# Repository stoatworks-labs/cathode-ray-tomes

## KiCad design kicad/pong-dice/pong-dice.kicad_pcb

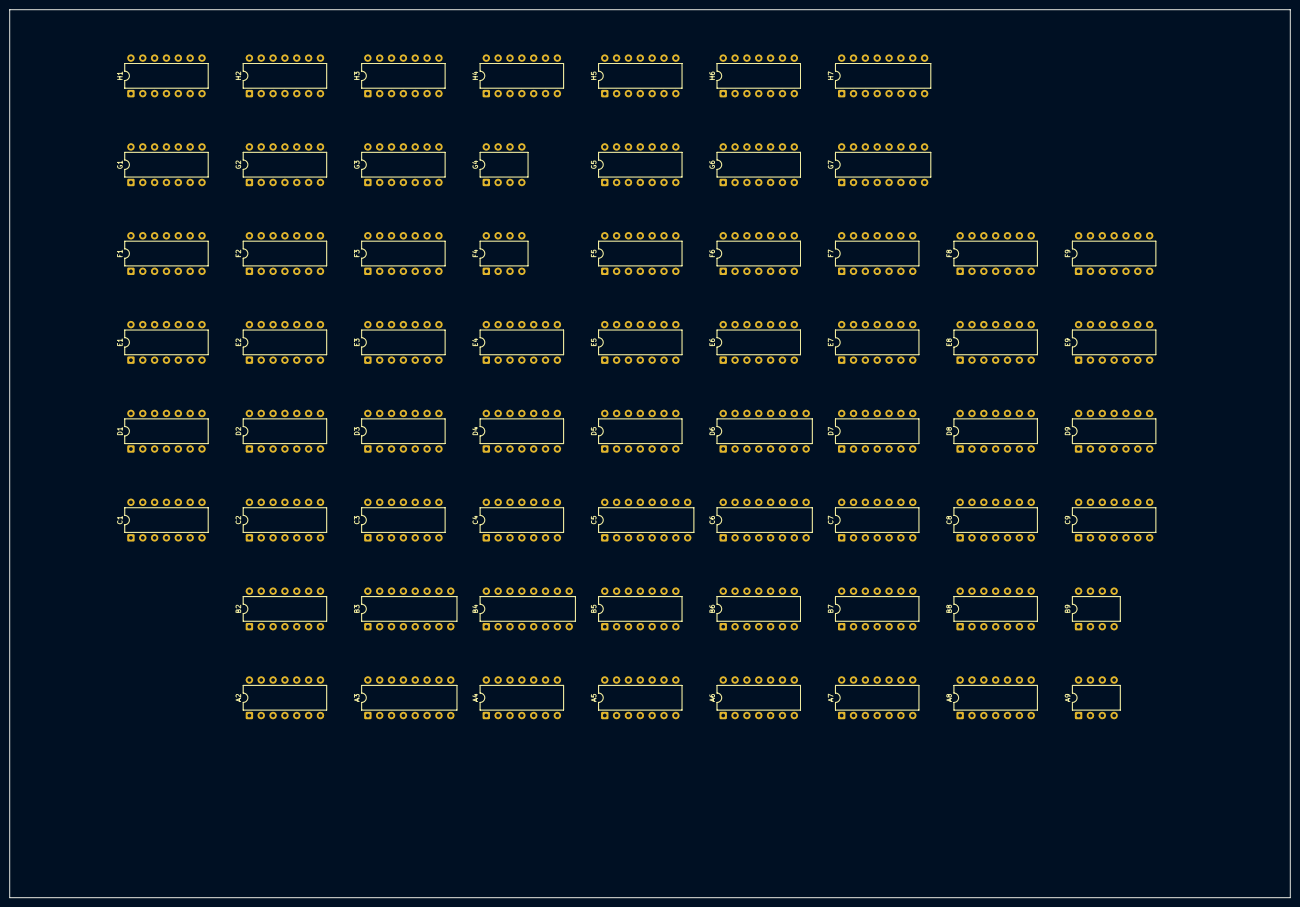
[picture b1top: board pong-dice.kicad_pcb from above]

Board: 2 copper layers, 274.6 x 190.4 mm, 66 parts (0 on the bottom side), 195 nets, no tracks yet.

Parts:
A2: 74107; DIP-14_W7.62mm
A3: 9316; DIP-16_W7.62mm
A4: 7486; DIP-14_W7.62mm
A5: 7474; DIP-14_W7.62mm
A6: 7450; DIP-14_W7.62mm
A7: 7420; DIP-14_W7.62mm
A8: 7493; DIP-14_W7.62mm
A9: 555; DIP-8_W7.62mm
B2, B7: 7400; DIP-14_W7.62mm
B3: 9316; DIP-16_W7.62mm
B4: 7483; DIP-16_W7.62mm
B5: 7474; DIP-14_W7.62mm
B6: 7450; DIP-14_W7.62mm
B8: 7493; DIP-14_W7.62mm
B9: 555; DIP-8_W7.62mm
C1, C3: 7400; DIP-14_W7.62mm
C2: 7474; DIP-14_W7.62mm
C4: 7410; DIP-14_W7.62mm
C5: 7448; DIP-16_W7.62mm
C6: 74153; DIP-16_W7.62mm
C7: 7490; DIP-14_W7.62mm
C8: 74107; DIP-14_W7.62mm
C9: 7404; DIP-14_W7.62mm
D1: 7404; DIP-14_W7.62mm
D2: 7402; DIP-14_W7.62mm
D3: 7430; DIP-14_W7.62mm
D4, D5, D8: 7410; DIP-14_W7.62mm
D6: 74153; DIP-16_W7.62mm
D7: 7490; DIP-14_W7.62mm
D9: 74107; DIP-14_W7.62mm
E1, E6: 7400; DIP-14_W7.62mm
E2: 7410; DIP-14_W7.62mm
E3, E5: 7427; DIP-14_W7.62mm
E4: 7404; DIP-14_W7.62mm
E7: 7474; DIP-14_W7.62mm
E8, E9: 7493; DIP-14_W7.62mm
F1, F8, F9: 7493; DIP-14_W7.62mm
F2: 7425; DIP-14_W7.62mm
F3, F6: 74107; DIP-14_W7.62mm
F4: 555; DIP-8_W7.62mm
F5: 7402; DIP-14_W7.62mm
F7: 7430; DIP-14_W7.62mm
G1: 7402; DIP-14_W7.62mm
G2: 7427; DIP-14_W7.62mm
G3: 7400; DIP-14_W7.62mm
G4: 555; DIP-8_W7.62mm
G5: 7410; DIP-14_W7.62mm
G6: 74107; DIP-14_W7.62mm
G7: 9316; DIP-16_W7.62mm
H1, H4, H5: 7400; DIP-14_W7.62mm
H2: 74107; DIP-14_W7.62mm
H3: 7474; DIP-14_W7.62mm
H6: 7420; DIP-14_W7.62mm
H7: 9316; DIP-16_W7.62mm

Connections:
+5V: A2.14, A3.16, A4.14, A5.14, A7.14, A8.5, A9.8, B2.14, B3.16, B4.5, B5.14, B7.14, B8.5, B9.8, C1.14, C2.14, C3.14, C4.14, C5.16, C6.16, C7.5, C8.14, C9.14, D1.14, D2.14, D3.14, D4.14, D5.14, D6.16, D7.5, D8.14, D9.14, E1.14, E2.14, E3.14, E4.14, E5.14, E6.14, E7.14, E8.5, E9.5, F1.5, F3.14, F4.8, F5.14, F6.14, F7.14, F8.5, F9.5, G1.14, G2.14, G3.14, G4.8, G5.14, G6.14, G7.16, H1.14, H2.14, H3.14, H4.14, H5.14, H6.14, H7.16
A2-2: A2.2, B6.9
A2-3: A2.3, A4.4, A4.10, B6.1
A3-2: A3.2, B3.2, B7.5, B7.10, H5.11
A3-7: A3.7, B2.5, B3.15
A3-9: A3.9, B2.6, B3.9
A3-13: A3.13, C3.4
A3-14: A3.14, C3.2
A3-15: A3.15, B2.4, C2.3, E2.5
A4-5: A4.5, A5.5
A4-6: A4.6, B4.8
A4-8: A4.8, B4.10
A4-9: A4.9, A5.9
A5-1: A5.1, A5.13, B5.1, D1.6
A5-2: A5.2, A6.6
A5-12: A5.12, A6.8
A6-1: A6.1, A7.9, B8.9
A6-3: A6.3, A7.12, B8.8
A6-4: A6.4, A7.4, A8.8
A6-10: A6.10, A7.1, A8.9
A7-2: A7.2, A8.1, A8.12
A7-5: A7.5, A8.11, B6.4
A7-6: A7.6, B7.9, B7.12
A7-8: A7.8, B7.2, B7.4
A7-10: A7.10, B8.1, B8.12
A7-13: A7.13, B6.3, B8.11
A8-2: A8.2, A8.3, A9.3, C9.1
A8-14: A8.14, B7.8
ATTRACT: C1.13, D1.4, D1.5
ATTRACT_n: C1.4, D1.3, D2.1, E1.2, E1.4, H3.4
B2-1: B2.1, D8.12
B2-2: B2.2, D8.6
B2-3: B2.3, D2.2, E4.9, E5.2
B2-9: B2.9, G3.3, H3.10
B2-10: B2.10, G3.11, H3.13
B3-3: B3.3, B4.9
B3-4: B3.4, B4.6
B3-5: B3.5, B4.2
B3-6: B3.6, B4.15
B3-11: B3.11, E2.4
B3-12: B3.12, E2.3
B4-3: B4.3, B6.8, C4.1, C4.2, C4.13
B4-11: B4.11, C4.12
B5-2: B5.2, B6.6
B5-5: B5.5, B6.13
B5-6: B5.6, B6.10
B5-8: B5.8, E1.5
B5-9: B5.9, F3.13
B5-11: B5.11, F2.9, G2.8, G3.13
B5-12: B5.12, B5.13, E5.12
B7-1: B7.1, C9.4
B7-3: B7.3, G2.11
B7-6: B7.6, B8.14
B7-11: B7.11, G2.1
B7-13: B7.13, C9.2
B8-2: B8.2, B8.3, B9.3, C9.3
C1-5: C1.5, C4.6
C1-11: C1.11, D1.1
C1-12: C1.12, C3.10, G4.3
C2-6: C2.6, C3.1, E1.13
C3-3: C3.3, C4.4
C3-5: C3.5, F3.3
C3-6: C3.6, C4.3
C3-8: C3.8, C4.5
C3-11: C3.11, D2.5
C4-8: C4.8, D3.4
C4-9: C4.9, D2.4, D5.1
C4-10: C4.10, D4.1, D4.5, D4.10, E4.6
C4-11: C4.11, C5.12
C5-1: C5.1, C6.9
C5-2: C5.2, D6.7
C5-4: C5.4, F2.6
C5-6: C5.6, D6.9
C5-7: C5.7, C6.7
C5-9: C5.9, D5.9
C5-10: C5.10, D5.5
C5-11: C5.11, D5.2
C5-13: C5.13, D4.9
C5-14: C5.14, D4.3
C5-15: C5.15, D4.2
C6-3: C6.3, D7.1, D7.12, D8.3
C6-5: C6.5, C7.1, C7.12, D8.1
C6-10: C6.10, C8.2, D6.6, D6.10
C6-11: C6.11, C7.9
C6-12: C6.12, C8.6, D6.4, D6.12
C6-13: C6.13, D7.9
C7-8: C7.8, D6.5
C7-11: C7.11, C8.12, D6.11
C7-14: C7.14, F5.4
C8-3: C8.3, D8.13
C8-5: C8.5, D8.5
C8-9: C8.9, D6.13, D7.11
CLK: E7.11, F3.9, F6.3, F8.14, G7.2, H7.2
D1-2: D1.2, H3.11
D1-12: D1.12, E1.1
D1-13: D1.13, E6.5, E6.8, G4.2
D2-6: D2.6, E4.4, E5.5, E5.9
D2-8: D2.8, E3.6
D2-9: D2.9, E3.8
D2-10: D2.10, F2.5
D3-2: D3.2, D5.12
D3-3: D3.3, D5.6
D3-5: D3.5, D5.8
D3-6: D3.6, D4.6
D3-11: D3.11, D4.8
D3-12: D3.12, D4.12
D4-4: D4.4, D5.3, E4.2
D4-11: D4.11, E5.6
D4-13: D4.13, D5.11, E5.8
D6-3: D6.3, D7.8
D7-14: D7.14, F5.1
D8-8: D8.8, E7.2
E1-3: E1.3, F5.3, F5.6
E1-6: E1.6, G6.10, G7.1, H7.1
E1-8: E1.8, E1.12, H1.13
E1-9: E1.9, F1.8, G1.11
E1-10: E1.10, F1.11, G1.12
E1-11: E1.11, F1.14
E2-8: E2.8, E3.9, E3.10, E3.11
E2-9: E2.9, E3.5, E3.12
E2-12: E2.12, E4.1
E4-13: E4.13, F2.8
E5-13: E5.13, F4.3
E6-1: E6.1, E6.2, E6.6, F1.2, F1.3
E6-3: E6.3, F4.2
E7-12: E7.12, F7.8
F1-1: F1.1, F1.12
F2-1: F2.1, G1.1
F2-12: F2.12, G2.12, G3.1
F2-13: F2.13, G1.4, G3.2, G3.12
F3-6: F3.6, G3.5
F5-2: F5.2, H3.8, H3.12, H4.5
F5-5: F5.5, H3.9, H4.13
G1-10: G1.10, H2.9, H2.12
G1-13: G1.13, H1.1, H1.2
G2-5: G2.5, G3.6
G2-9: G2.9, G2.13, G3.8
G3-9: G3.9, H3.6
G5-6: G5.6, H5.4
G5-8: G5.8, G7.9, H7.9
G5-9: G5.9, G6.9, H6.12, H7.15
G5-10: G5.10, G7.15, H7.7
G5-11: G5.11, G6.5, H6.13
G5-13: G5.13, H5.3
G7-3: G7.3, H4.8
G7-4: G7.4, H4.6, H4.9
G7-11: G7.11, H6.10
G7-12: G7.12, H6.9
GND: A2.7, A3.3, A3.4, A3.5, A3.6, A3.8, A4.7, A5.7, A7.7, A8.10, A9.1, B2.7, B3.8, B4.1, B4.12, B4.13, B4.16, B5.7, B7.7, B8.10, B9.1, C1.7, C2.7, C3.7, C4.7, C5.8, C6.1, C6.8, C6.15, C7.6, C7.7, C7.10, C8.7, C9.7, D1.7, D2.7, D3.7, D4.7, D5.7, D6.1, D6.8, D6.15, D7.6, D7.7, D7.10, D8.7, D9.7, E1.7, E2.7, E3.7, E4.7, E5.7, E6.7, E7.7, E8.10, E9.10, F1.10, F3.7, F4.1, F5.7, F6.7, F7.7, F8.10, F9.10, G1.7, G2.7, G3.7, G4.1, G5.7, G6.7, G7.5, G7.8, H1.7, H2.4, H2.7, H3.7, H4.7, H5.7, H6.7, H7.3, H7.4, H7.5, H7.8
H1: F8.1, F8.12
H1-3: H1.3, H1.4, H1.12
H1-6: H1.6, H2.13
H1-8: H1.8, H2.10
H1-9: H1.9, H1.11
H2: F7.6, F8.9
H2-1: H2.1, H2.5, H4.1
H2-3: H2.3, H4.2
H2-11: H2.11, H4.3, H4.4, H4.12
H4: C3.12, E5.10, F7.5, F8.8, H3.3
H4-10: H4.10, H4.11
H8: C3.13, E5.11, F8.11, F9.14
H16: E2.13, E4.3, F9.1, F9.12, G5.3
H32: C6.14, D6.14, F9.9, H5.13
H64: C6.2, D6.2, E2.10, E3.4, F7.11, F9.8, G5.4, G5.5
H128: E3.1, E3.2, E3.13, F6.9, F7.12, F9.11, G3.10, H3.2
H256: A6.5, A6.9, B6.5, E2.11, E3.3, F3.8, F6.5, F7.1, G2.10, G3.4
H256_n: A6.2, A6.13, B6.2, F3.11, F6.6, G1.8, G2.2
HBLANK: E6.10, H5.5, H5.8, H5.12
HBLANK_n: G7.10, H5.6, H5.9
HIT: A5.3, A5.11, B2.8, B2.12, B2.13, B5.3
HIT_n: A2.13, B2.11, C2.1
HRESET: E7.3, E7.8, E8.14, F8.2, F8.3, F9.2, F9.3
HRESET_n: E7.9, F6.10, H5.10
HVID: E6.9, H6.6
HVID_n: G1.5, H6.1, H6.2, H6.4, H6.5, H6.8
NET: F2.10, G2.6
RUN_n: D2.3, E5.1
SRST: C7.2, C7.3, C9.12, D7.2, D7.3
SRST_n: C8.10, C8.13, C9.13, E6.4
V1: D8.10, E8.1, E8.12
V4: D8.11, E2.1, E5.4, E8.8, G2.3, G5.2
V8: E2.2, E5.3, E8.11, E9.14, H5.1, H5.2
V16: D5.4, D5.10, D5.13, E4.5, E9.1, E9.12, F5.12
V32: C3.9, E9.9, G1.2, G1.3
V64: E9.8, F2.2
V128: D9.9, E9.11, F2.4
V256: D8.9, D9.5
V256_n: A9.2, B9.2, D9.6
VBLANK: A2.12, F3.12, F5.9, F5.13, G2.4, G5.1
VBLANK_n: B3.10, F5.10, F5.11
VCC: A3.1, A3.10, A5.4, A5.10, A9.4, B3.1, B3.7, B4.4, B4.7, B5.4, B5.10, B9.4, C2.2, C2.4, C5.3, C5.5, C6.4, C6.6, C8.1, C8.4, C8.8, C8.11, D3.1, D9.8, D9.11, E7.1, E7.4, E7.10, E7.13, F3.10, F4.4, F6.1, F6.4, F6.8, F6.11, F6.13, F7.2, F7.3, F7.4, G4.4, G6.8, G6.11, G7.6, G7.7, H2.8, H3.1, H7.6, H7.10
VRESET: E7.6, E8.2, E8.3, E9.2, E9.3, F5.8, G1.9, H1.5, H1.10
VRESET_n: D9.10, E7.5
VVID: A2.1, A2.4, D2.13, F3.1
VVID_n: D2.11, D2.12, E2.6, F3.4, G1.6

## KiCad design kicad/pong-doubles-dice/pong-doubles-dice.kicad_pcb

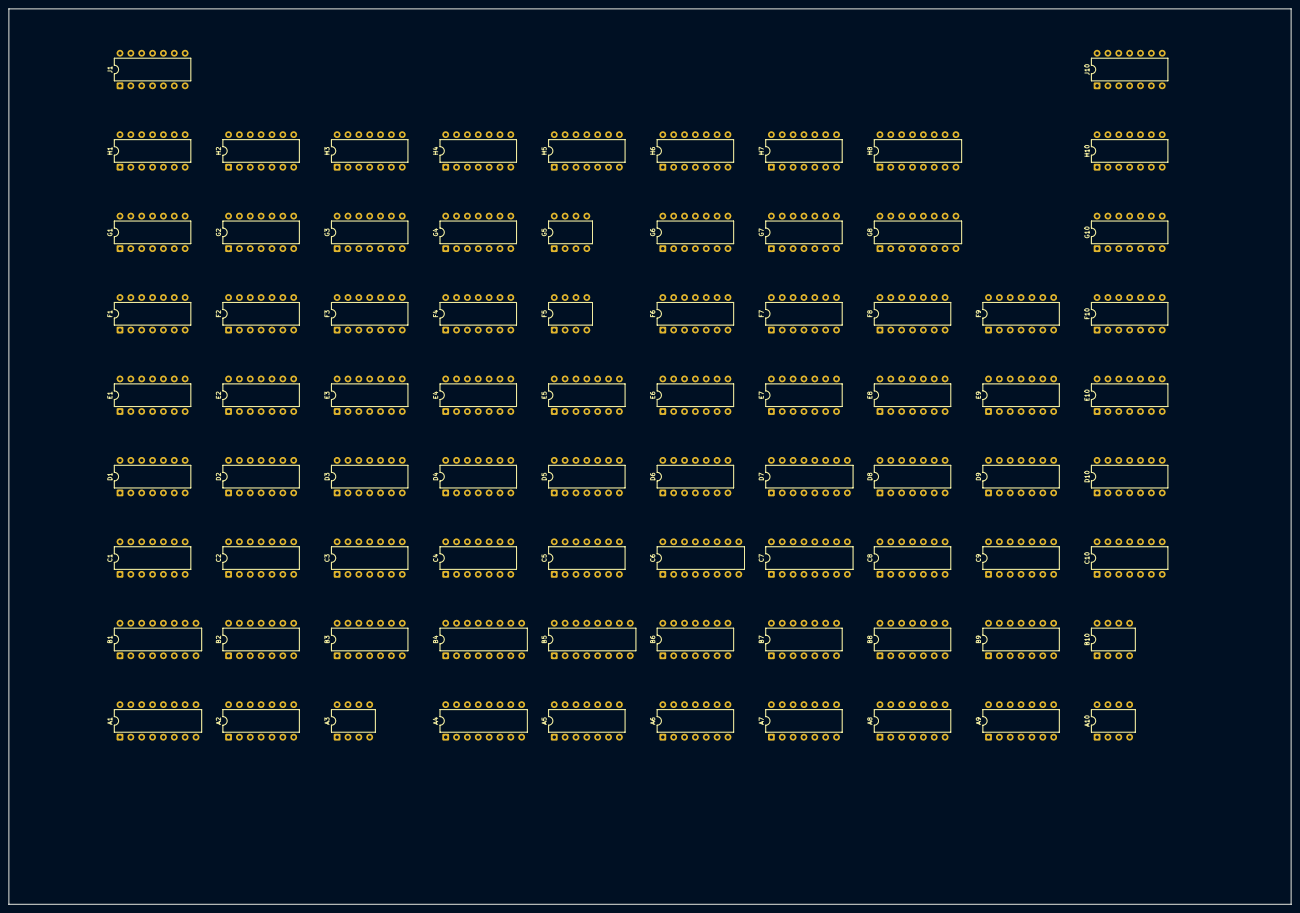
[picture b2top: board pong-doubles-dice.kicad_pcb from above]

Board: 2 copper layers, 300.0 x 209.5 mm, 80 parts (0 on the bottom side), 241 nets, no tracks yet.

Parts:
A1: 74153; DIP-16_W7.62mm
A2, A8: 7420; DIP-14_W7.62mm
A3, A10: 555; DIP-8_W7.62mm
A4: 9316; DIP-16_W7.62mm
A5: 7486; DIP-14_W7.62mm
A6: 7474; DIP-14_W7.62mm
A7, A9: 7493; DIP-14_W7.62mm
B1: 74153; DIP-16_W7.62mm
B2, B6: 7474; DIP-14_W7.62mm
B3, B8: 7400; DIP-14_W7.62mm
B4: 9316; DIP-16_W7.62mm
B5: 7483; DIP-16_W7.62mm
B7: 7450; DIP-14_W7.62mm
B9: 556; DIP-14_W7.62mm
B10: 555; DIP-8_W7.62mm
C1: 7493; DIP-14_W7.62mm
C2, C4: 7400; DIP-14_W7.62mm
C3: 7474; DIP-14_W7.62mm
C5: 7410; DIP-14_W7.62mm
C6: 7448; DIP-16_W7.62mm
C7: 74153; DIP-16_W7.62mm
C8: 7490; DIP-14_W7.62mm
C9: 74107; DIP-14_W7.62mm
C10: 7404; DIP-14_W7.62mm
D1: 7493; DIP-14_W7.62mm
D2: 7404; DIP-14_W7.62mm
D3: 7402; DIP-14_W7.62mm
D4: 7430; DIP-14_W7.62mm
D5, D6, D9: 7410; DIP-14_W7.62mm
D7: 74153; DIP-16_W7.62mm
D8: 7490; DIP-14_W7.62mm
D10: 74107; DIP-14_W7.62mm
E1, E2, E7: 7400; DIP-14_W7.62mm
E3: 7410; DIP-14_W7.62mm
E4, E6: 7427; DIP-14_W7.62mm
E5: 7404; DIP-14_W7.62mm
E8: 7474; DIP-14_W7.62mm
E9, E10: 7493; DIP-14_W7.62mm
F1: 7427; DIP-14_W7.62mm
F2, F9, F10: 7493; DIP-14_W7.62mm
F3: 7425; DIP-14_W7.62mm
F4, F7: 74107; DIP-14_W7.62mm
F5: 555; DIP-8_W7.62mm
F6: 7402; DIP-14_W7.62mm
F8: 7430; DIP-14_W7.62mm
G1: 7404; DIP-14_W7.62mm
G2: 7402; DIP-14_W7.62mm
G3: 7427; DIP-14_W7.62mm
G4: 7400; DIP-14_W7.62mm
G5: 555; DIP-8_W7.62mm
G6: 7410; DIP-14_W7.62mm
G7: 74107; DIP-14_W7.62mm
G8: 9316; DIP-16_W7.62mm
G10: 7474; DIP-14_W7.62mm
H1: 7402; DIP-14_W7.62mm
H2, H5, H6: 7400; DIP-14_W7.62mm
H3: 74107; DIP-14_W7.62mm
H4, H10: 7474; DIP-14_W7.62mm
H7: 7420; DIP-14_W7.62mm
H8: 9316; DIP-16_W7.62mm
J1: 7474; DIP-14_W7.62mm
J10: 7400; DIP-14_W7.62mm

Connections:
+5V: A1.16, A2.14, A3.8, A4.16, A5.14, A6.14, A7.5, A8.14, A9.5, A10.8, B1.16, B2.14, B3.14, B4.16, B5.5, B6.14, B8.14, B9.14, B10.8, C1.5, C2.14, C3.14, C4.14, C5.14, C6.16, C7.16, C8.5, C9.14, C10.14, D1.5, D2.14, D3.14, D4.14, D5.14, D6.14, D7.16, D8.5, D9.14, D10.14, E1.14, E2.14, E3.14, E4.14, E5.14, E6.14, E7.14, E8.14, E9.5, E10.5, F1.14, F2.5, F4.14, F5.8, F6.14, F7.14, F8.14, F9.5, F10.5, G1.14, G2.14, G3.14, G4.14, G5.8, G6.14, G7.14, G8.16, G10.14, H1.14, H2.14, H3.14, H4.14, H5.14, H6.14, H7.14, H8.16, H10.14, J1.14, J10.14
A1-3: A1.3, A2.2, C1.8
A1-4: A1.4, A8.4, A9.8
A1-5: A1.5, A2.12, D1.8
A1-6: A1.6, A7.8, A8.12
A1-7: A1.7, A6.2
A1-9: A1.9, B6.2
A1-10: A1.10, A7.11, A8.13, B7.3
A1-11: A1.11, A2.13, D1.11
A1-12: A1.12, A8.5, A9.11, B7.4
A1-13: A1.13, A2.1, C1.11
A2-4: A2.4, B1.3, C1.9
A2-5: A2.5, C1.1, C1.12
A2-6: A2.6, E1.5, E1.10
A2-8: A2.8, E1.2, E1.13
A2-9: A2.9, B1.5, D1.9
A2-10: A2.10, D1.1, D1.12
A3-3: A3.3, D2.11
A4-7: A4.7, B3.5, B4.15
A4-9: A4.9, B3.6, B4.9
A4-13: A4.13, C4.4
A4-14: A4.14, C4.2
A4-15: A4.15, B3.4, C3.3, E3.5
A5-4: A5.4, A5.10, B7.1, D10.3
A5-5: A5.5, A6.6
A5-6: A5.6, B5.8
A5-8: A5.8, B5.10
A5-9: A5.9, A6.8
A6-1: A6.1, A6.13, B6.1, D2.6
A6-12: A6.12, B1.7
A7-1: A7.1, A7.12, A8.10
A7-2: A7.2, A7.3, B10.3, C10.3
A7-9: A7.9, A8.9, B1.6
A7-14: A7.14, B8.6
A8-1: A8.1, A9.9, B1.4
A8-2: A8.2, A9.1, A9.12
A8-6: A8.6, B8.9, B8.12
A8-8: A8.8, B8.2, B8.5
A9-2: A9.2, A9.3, A10.3, C10.1
A9-14: A9.14, B8.8
ATTRACT: C2.13, D2.3, D2.5, E6.1, G10.2, G10.9, H10.3, J10.1
ATTRACT_n: C2.4, D2.4, E2.2, E2.4, H4.4, J1.1
B2-1: B2.1, B2.2, C10.6
B2-3: B2.3, D2.10
B2-5: B2.5, C3.11
B2-6: B2.6, H10.1
B2-12: B2.12, C2.8
B2-13: B2.13, D3.1
B3-1: B3.1, D9.12
B3-2: B3.2, D9.6
B3-3: B3.3, E6.2, G10.11
B3-9: B3.9, G4.3, H4.10
B3-10: B3.10, G4.11, H4.13
B4-3: B4.3, B5.9
B4-4: B4.4, B5.6
B4-5: B4.5, B5.2
B4-6: B4.6, B5.15
B4-11: B4.11, E3.4
B4-12: B4.12, E3.3
B5-3: B5.3, B7.8, C5.1, C5.2, C5.13
B5-11: B5.11, C5.12
B6-5: B6.5, B7.10
B6-6: B6.6, B7.13
B6-8: B6.8, E2.5
B6-9: B6.9, F4.13
B6-11: B6.11, G3.8, H1.3
B6-12: B6.12, B6.13, E6.12
B7-9: B7.9, D10.2
B8-1: B8.1, C10.4
B8-3: B8.3, G3.11
B8-11: B8.11, G3.1
B8-13: B8.13, C10.2
B9-5: B9.5, D1.2, D1.3, G1.1
B9-9: B9.9, C1.2, C1.3, G1.3
C1-14: C1.14, E1.6
C2-5: C2.5, C5.6
C2-9: C2.9, D2.8
C2-11: C2.11, D2.1
C2-12: C2.12, C4.10, G5.3
C3-6: C3.6, C4.1, E2.13
C3-9: C3.9, J1.10
C3-12: C3.12, H10.6, J10.5
C4-3: C4.3, C5.4
C4-5: C4.5, F4.3
C4-6: C4.6, C5.3
C4-8: C4.8, C5.5
C4-11: C4.11, D3.5
C5-8: C5.8, D4.4
C5-9: C5.9, D3.4, D6.1
C5-10: C5.10, D5.1, D5.5, D5.10, E5.6
C5-11: C5.11, C6.12
C6-1: C6.1, C7.9
C6-2: C6.2, D7.7
C6-4: C6.4, F3.6
C6-6: C6.6, D7.9
C6-7: C6.7, C7.7
C6-9: C6.9, D6.9
C6-10: C6.10, D6.5
C6-11: C6.11, D6.2
C6-13: C6.13, D5.9
C6-14: C6.14, D5.3
C6-15: C6.15, D5.2
C7-3: C7.3, D8.1, D8.12, D9.3
C7-5: C7.5, C8.1, C8.12, D9.1
C7-10: C7.10, C9.2, D7.6, D7.10
C7-11: C7.11, C8.9
C7-12: C7.12, C9.6, D7.4, D7.12
C7-13: C7.13, D8.9
C8-8: C8.8, D7.5
C8-11: C8.11, C9.12, D7.11
C8-14: C8.14, F6.4
C9-3: C9.3, D9.13
C9-5: C9.5, D9.5
C9-9: C9.9, D7.13, D8.11
CLK: E8.11, F4.9, F7.3, F9.14, G8.2, H8.2
D1-14: D1.14, E1.3
D2-2: D2.2, H4.11
D2-12: D2.12, E2.1
D2-13: D2.13, E7.5, E7.8, G5.2
D3-6: D3.6, E5.4, E6.5, E6.9
D3-8: D3.8, E4.6
D3-9: D3.9, E4.8
D3-10: D3.10, F3.5
D4-2: D4.2, D6.12
D4-3: D4.3, D6.6
D4-5: D4.5, D6.8
D4-6: D4.6, D5.6
D4-11: D4.11, D5.8
D4-12: D4.12, D5.12
D5-4: D5.4, D6.3, E5.2
D5-11: D5.11, E6.6
D5-13: D5.13, D6.11, E6.8
D7-3: D7.3, D8.8
D8-14: D8.14, F6.1
D9-8: D9.8, E8.2
E1-8: E1.8, F1.10
E1-9: E1.9, G1.4
E1-11: E1.11, F1.1
E1-12: E1.12, G1.2
E2-3: E2.3, F6.3, F6.6
E2-6: E2.6, G7.10, G8.1, H8.1
E2-8: E2.8, E2.12, H2.13
E2-9: E2.9, F2.8, G2.11
E2-10: E2.10, F2.11, G2.12
E2-11: E2.11, F2.14
E3-8: E3.8, E4.9, E4.10, E4.11
E3-9: E3.9, E4.5, E4.12
E3-12: E3.12, E5.1
E5-13: E5.13, F3.8
E6-13: E6.13, F5.3
E7-1: E7.1, E7.2, E7.6, F2.2, F2.3
E7-3: E7.3, F5.2
E8-12: E8.12, F8.8
F1-3: F1.3, G1.6, J1.2
F1-4: F1.4, J1.9
F1-5: F1.5, J1.6
F1-6: F1.6, H1.8, H1.9
F1-8: F1.8, H1.5
F1-11: F1.11, F1.13, H1.10
F1-12: F1.12, H1.2
F2-1: F2.1, F2.12
F3-1: F3.1, G2.1
F3-9: F3.9, G1.12, G4.13
F3-12: F3.12, G1.10, G4.1
F3-13: F3.13, G2.4, G4.2, G4.12
F4-6: F4.6, G4.5
F6-2: F6.2, H4.8, H4.12, H5.5
F6-5: F6.5, H4.9, H5.13
G1-11: G1.11, H1.4
G1-13: G1.13, H1.1
G2-10: G2.10, H3.9, H3.12
G2-13: G2.13, H2.1, H2.2
G3-5: G3.5, G4.6
G3-9: G3.9, G3.13, G4.8, J1.11
G3-12: G3.12, H1.6
G4-9: G4.9, H4.6
G6-6: G6.6, H6.4
G6-8: G6.8, G8.9, H8.9
G6-9: G6.9, G7.9, H7.12, H8.15
G6-10: G6.10, G8.15, H8.7
G6-11: G6.11, G7.5, H7.13
G6-13: G6.13, H6.3
G8-3: G8.3, H5.8
G8-4: G8.4, H5.6, H5.9
G8-11: G8.11, H7.10
G8-12: G8.12, H7.9
G10-1: G10.1, H10.8
G10-3: G10.3, J10.8
G10-5: G10.5, H10.12
G10-10: G10.10, H6.11, H10.4
GND: A1.1, A1.8, A1.15, A2.7, A3.1, A4.3, A4.4, A4.5, A4.6, A4.8, A5.7, A6.7, A7.10, A8.7, A9.10, A10.1, B1.1, B1.8, B2.7, B3.7, B4.8, B5.1, B5.12, B5.13, B5.16, B6.7, B8.7, B9.7, B10.1, C1.10, C2.7, C3.7, C4.7, C5.7, C6.8, C7.1, C7.8, C7.15, C8.6, C8.7, C8.10, C9.7, C10.7, D1.10, D2.7, D3.7, D4.7, D5.7, D6.7, D7.1, D7.8, D7.15, D8.6, D8.7, D8.10, D9.7, D10.7, E1.7, E2.7, E3.7, E4.7, E5.7, E6.7, E7.7, E8.7, E9.10, E10.10, F1.7, F2.10, F4.7, F5.1, F6.7, F7.7, F8.7, F9.10, F10.10, G1.7, G2.7, G3.7, G4.7, G5.1, G6.7, G7.7, G8.5, G8.8, G10.7, H1.7, H2.7, H3.4, H3.7, H4.7, H5.7, H6.7, H7.7, H8.3, H8.4, H8.5, H8.8, H10.7, J1.7, J10.7
H1: F9.1, F9.12
H2: F8.6, F9.9
H2-3: H2.3, H2.4, H2.12
H2-6: H2.6, H3.13
H2-8: H2.8, H3.10
H2-9: H2.9, H2.11
H3-1: H3.1, H3.5, H5.1
H3-3: H3.3, H5.2
H3-11: H3.11, H5.3, H5.4, H5.12
H4: C4.12, E6.10, F8.5, F9.8, H4.3, J1.3
H5-10: H5.10, H5.11
H6-12: H6.12, H6.13
H8: C4.13, E6.11, F9.11, F10.14
H10-5: H10.5, J10.2
H10-9: H10.9, J10.4
H16: B2.11, E3.13, E5.3, F10.1, F10.12, G6.3
H32: C2.10, C7.14, D7.14, F10.9
H64: A1.14, B1.14, C7.2, D2.9, D3.3, D7.2, E3.10, E4.4, F8.12, F10.8, G1.5, G6.4, G6.5
H128: E4.1, E4.2, E4.13, F7.9, F8.11, F10.11, G4.10, H4.2
H256: A1.2, B1.2, B7.5, E3.11, E4.3, F1.2, F4.8, F7.5, F8.1, G3.10, G4.4, J1.13
H256_n: B7.2, F1.9, F4.11, F7.6, G2.8, G3.2
HBLANK: E7.10, H6.5, H6.8
HBLANK_n: D3.2, G8.10, H6.6, H6.9
HIT: A6.3, A6.11, B3.8, B3.12, B3.13, B6.3
HIT_n: B3.11, C3.1, D10.13
HRESET: E8.3, E8.8, E9.14, F9.2, F9.3, F10.2, F10.3
HRESET_n: E8.9, F7.10, H6.10
HSYNC_n: A4.2, B2.8, B4.2, B8.4, B8.10, E1.1, E1.4
HVID: E7.9, H7.6
HVID_n: G2.5, H7.1, H7.2, H7.4, H7.5, H7.8
J10-9: J10.9, J10.10
NET: F3.10, G3.6
SRST: C8.2, C8.3, D8.2, D8.3, E5.8
SRST_n: C9.10, C9.13, E5.9, E7.4, G10.13, J10.6
V1: D9.10, E9.1, E9.12
V4: D9.11, E3.1, E6.4, E9.8, G3.3, G6.2
V8: E3.2, E6.3, E9.11, E10.14, H6.1, H6.2
V16: D6.4, D6.10, D6.13, E5.5, E10.1, E10.12, F6.12
V32: C4.9, E10.9, G2.2, G2.3
V64: E10.8, F3.2
V128: D10.9, E10.11, F3.4
V256: D9.9, D10.5, H10.11
V256_n: A10.2, B9.6, B9.8, B10.2, D10.6
VBLANK: D10.12, F4.12, F6.9, F6.13, G3.4, G6.1
VBLANK_n: B4.10, F6.10, F6.11
VCC: A3.4, A4.1, A4.10, A6.4, A6.10, A10.4, B2.4, B2.10, B4.1, B4.7, B5.4, B5.7, B6.4, B6.10, B9.4, B9.10, B10.4, C3.2, C3.4, C3.10, C3.13, C6.3, C6.5, C7.4, C7.6, C9.1, C9.4, C9.8, C9.11, D4.1, D10.8, D10.11, E8.1, E8.4, E8.10, E8.13, F4.10, F5.4, F7.1, F7.4, F7.8, F7.11, F7.13, F8.2, F8.3, F8.4, G5.4, G7.8, G7.11, G8.6, G8.7, G10.4, G10.12, H3.8, H4.1, H8.6, H8.10, H10.2, H10.10, H10.13, J1.4, J1.12
VRESET: E8.6, E9.2, E9.3, E10.2, E10.3, F6.8, G2.9, H2.5, H2.10
VRESET_n: D10.10, E8.5
VVID: D3.13, D10.1, D10.4, F4.1
VVID_n: D3.11, D3.12, E3.6, F4.4, G2.6
